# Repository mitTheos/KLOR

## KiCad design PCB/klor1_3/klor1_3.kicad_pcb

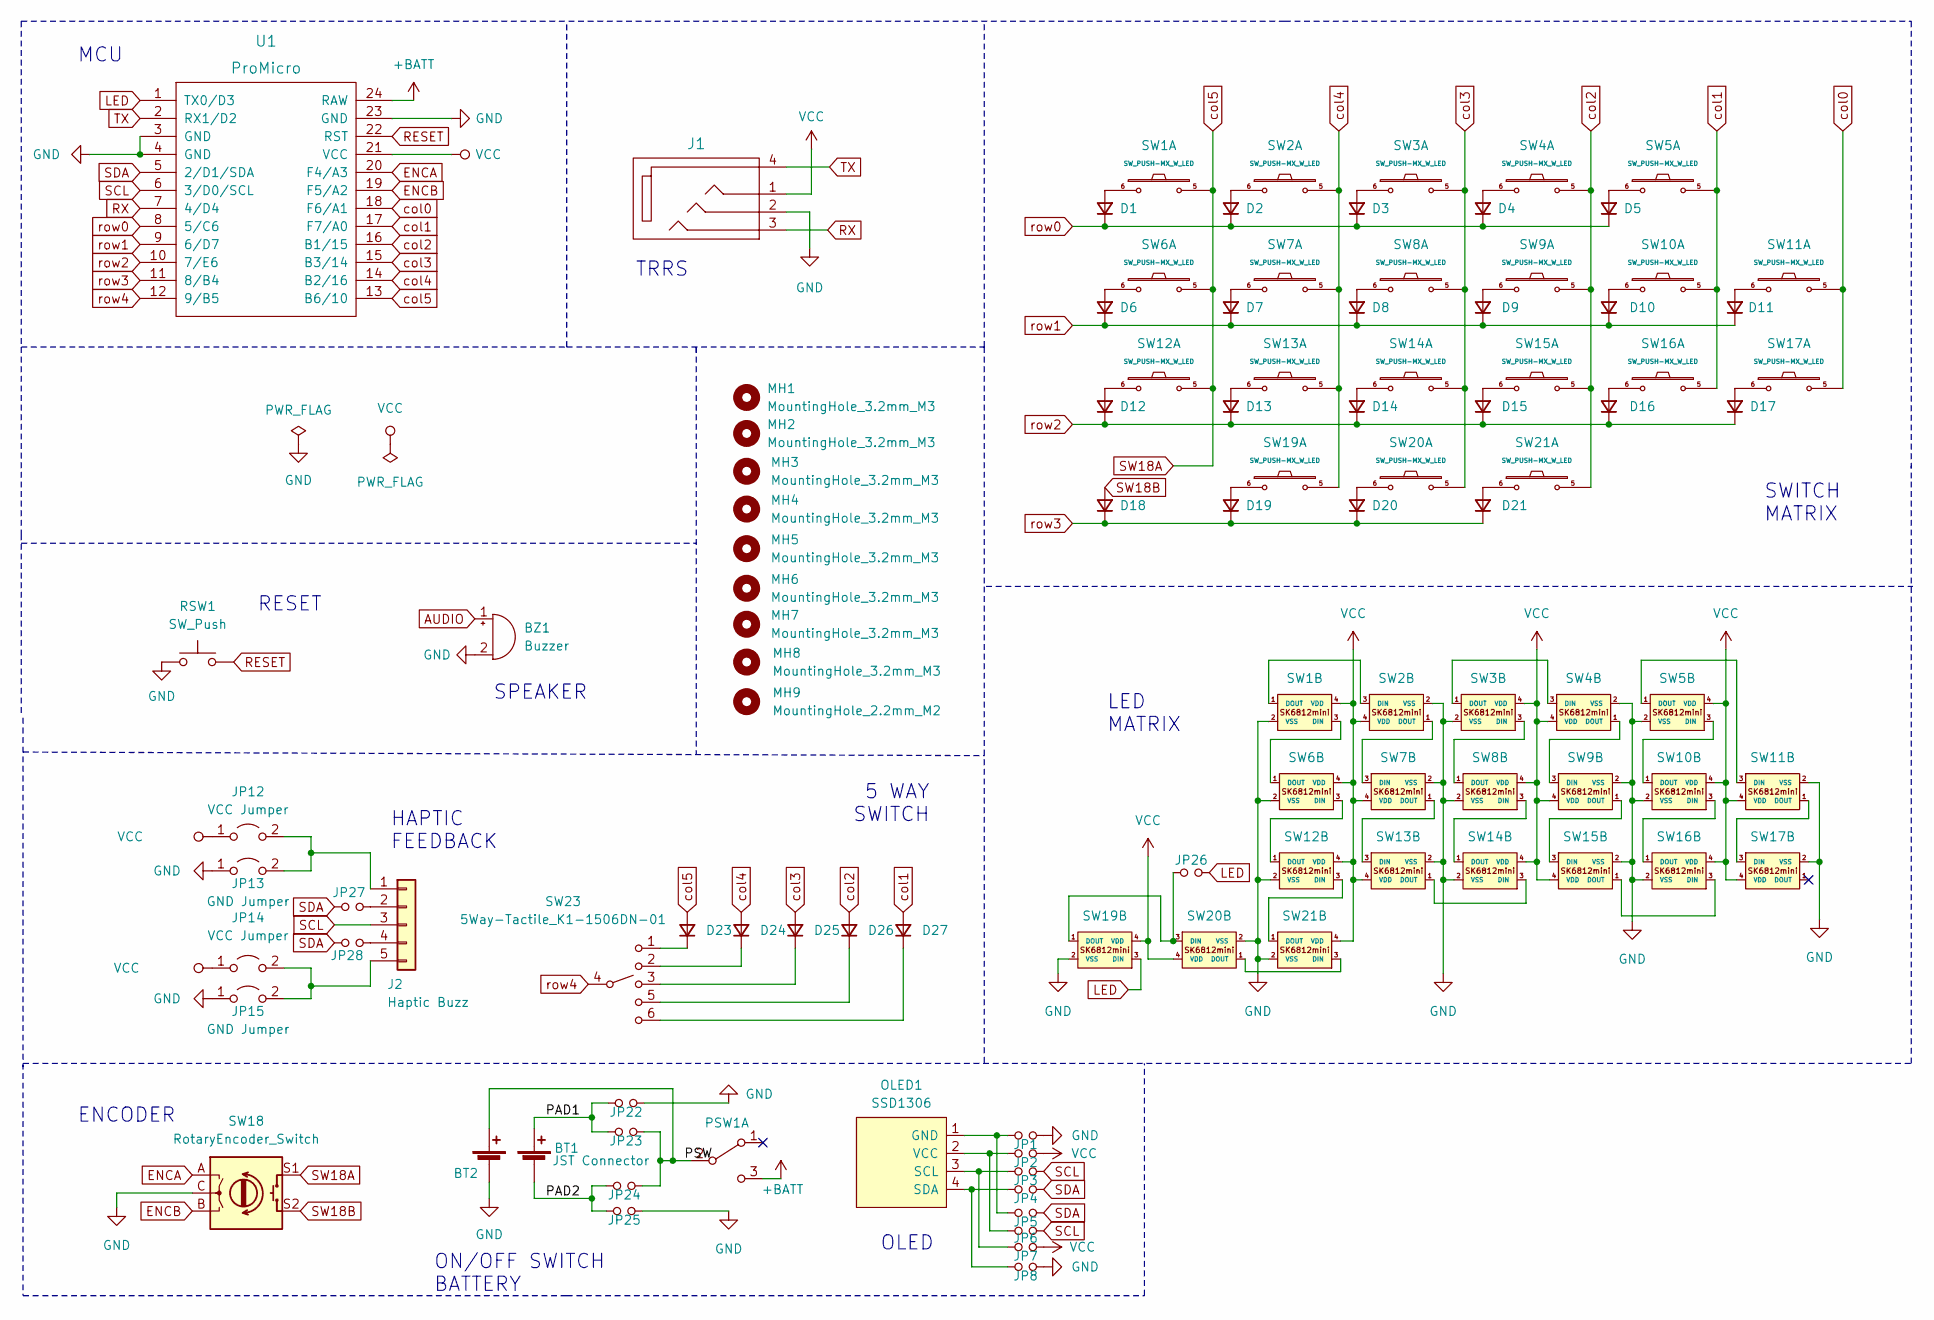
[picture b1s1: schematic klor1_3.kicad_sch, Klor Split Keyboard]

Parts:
BT1: JST Connector; JST_PH_reversible
BT2: Battery_Cell; custombatteryconnector_small
BZ1: Buzzer; Buzzer_Mallory_AST1109MLTRQ_reversible
D1, D2, D3, D4, D5, D6, D7, D8, D9, D10, D11, D12, D13, D14, D15, D16, D17, D18, D19, D20, D21, D23, D24, D25, D26, D27: D_Small; Diode_SOD123
J1: MJ-4PP-9
J2: Haptic Buzz; Pimoroni Haptic Buzz DRV2605L Driver
JP1, JP2, JP3, JP4, JP5, JP6, JP7, JP8, JP22, JP23, JP24, JP25, JP26, JP27, JP28: Device_Jumper_NO_Small; Jumper
JP12, JP14: VCC Jumper; Jumper
JP13, JP15: GND Jumper; Jumper
MH1, MH2, MH3, MH4, MH5, MH6, MH7, MH8: MountingHole_3.2mm_M3
MH9: MountingHole_2.2mm_M2
OLED1: SSD1306; SSD1306_128x64OLED
PSW1: SW_DPDT_x2; MSK12C02_reversible
RSW1: SW_Push; SW_Push_1P1T-MP_NO_Horizontal_Alps_SKRTLAE010_both_sides
SW1, SW2, SW3, SW4, SW5, SW6, SW7, SW8, SW9, SW10, SW11, SW12, SW13, SW14, SW15, SW16, SW17, SW19, SW20, SW21: SW_PUSH-MX_W_LED; SK6812MINI_and_cherry
SW18: RotaryEncoder_Switch; RotaryEncoder_Alps_EC11E-Switch_Vertical_H20mm-keebio_modif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
SW23: 5Way-Tactile_K1-1506DN-01; 5Way-K1-1506DN-01
U1: ProMicro

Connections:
+BATT: PSW1.3 (C), U1.24 (RAW)
/PAD1: BT1.1 (+), JP22.1, JP23.1
/PAD2: BT1.2 (-), JP24.1, JP25.1
/PSW: BT2.1 (+), JP23.2, JP24.2, PSW1.2 (B)
ENCA: SW18.A, U1.20 (F4/A3)
ENCB: SW18.B, U1.19 (F5/A2)
GND: BT2.2 (-), BZ1.2 (+), J1.2, JP1.2, JP8.2, JP13.1 (A), JP15.1 (A), JP22.2, JP25.2, RSW1.1, SW1.2 (VSS), SW2.2 (VSS), SW3.2 (VSS), SW4.2 (VSS), SW5.2 (VSS), SW6.2 (VSS), SW7.2 (VSS), SW8.2 (VSS), SW9.2 (VSS), SW10.2 (VSS), SW11.2 (VSS), SW12.2 (VSS), SW13.2 (VSS), SW14.2 (VSS), SW15.2 (VSS), SW16.2 (VSS), SW17.2 (VSS), SW18.C, SW19.2 (VSS), SW20.2 (VSS), SW21.2 (VSS), U1.3 (GND), U1.4 (GND), U1.23 (GND)
LED: JP26.2, SW19.3 (DIN), U1.1 (TX0/D3)
unnamed: D1.2 (A), SW1.6
unnamed: D2.2 (A), SW2.6
unnamed: D3.2 (A), SW3.6
unnamed: D4.2 (A), SW4.6
unnamed: D5.2 (A), SW5.6
unnamed: D6.2 (A), SW6.6
unnamed: D7.2 (A), SW7.6
unnamed: D8.2 (A), SW8.6
unnamed: D9.2 (A), SW9.6
unnamed: D10.2 (A), SW10.6
unnamed: D11.2 (A), SW11.6
unnamed: D12.2 (A), SW12.6
unnamed: D13.2 (A), SW13.6
unnamed: D14.2 (A), SW14.6
unnamed: D15.2 (A), SW15.6
unnamed: D16.2 (A), SW16.6
unnamed: D17.2 (A), SW17.6
unnamed: D19.2 (A), SW19.6
unnamed: D20.2 (A), SW20.6
unnamed: D21.2 (A), SW21.6
unnamed: D23.1 (K), SW23.1
unnamed: D24.1 (K), SW23.2
unnamed: D25.1 (K), SW23.3
unnamed: D26.1 (K), SW23.5
unnamed: D27.1 (K), SW23.6
unnamed: J2.1, JP12.2 (B), JP13.2 (B)
unnamed: J2.2, JP27.2
unnamed: J2.4, JP28.2
unnamed: J2.5, JP14.2 (B), JP15.2 (B)
unnamed: JP1.1, JP5.1, OLED1.1 (GND)
unnamed: JP3.1, JP7.1, OLED1.3 (SCL)
unnamed: JP4.1, JP8.1, OLED1.4 (SDA)
unnamed: JP2.1, JP6.1, OLED1.2 (VCC)
unnamed: SW1.3 (DIN), SW6.1 (DOUT)
unnamed: SW1.1 (DOUT), SW2.3 (DIN)
unnamed: SW2.1 (DOUT), SW7.3 (DIN)
unnamed: SW3.3 (DIN), SW8.1 (DOUT)
unnamed: SW3.1 (DOUT), SW4.3 (DIN)
unnamed: SW4.1 (DOUT), SW9.3 (DIN)
unnamed: SW10.3 (DIN), SW16.1 (DOUT)
unnamed: SW5.3 (DIN), SW10.1 (DOUT)
unnamed: SW5.1 (DOUT), SW11.3 (DIN)
unnamed: SW11.1 (DOUT), SW17.3 (DIN)
unnamed: SW12.3 (DIN), SW21.1 (DOUT)
unnamed: SW6.3 (DIN), SW12.1 (DOUT)
unnamed: SW7.1 (DOUT), SW13.3 (DIN)
unnamed: SW13.1 (DOUT), SW14.3 (DIN)
unnamed: SW8.3 (DIN), SW14.1 (DOUT)
unnamed: SW9.1 (DOUT), SW15.3 (DIN)
unnamed: SW15.1 (DOUT), SW16.3 (DIN)
unnamed: JP26.1, SW19.1 (DOUT), SW20.3 (DIN)
unnamed: SW20.1 (DOUT), SW21.3 (DIN)
RESET: RSW1.2, U1.22 (RST)
RX: J1.3, U1.7 (4/D4)
SCL: J2.3, JP3.2, JP6.2, U1.6 (3/D0/SCL)
SDA: JP4.2, JP5.2, JP27.1, JP28.1, U1.5 (2/D1/SDA)
SW18B: D18.2 (A), SW18.S2
TX: J1.4, U1.2 (RX1/D2)
VCC: J1.1, JP2.2, JP7.2, JP12.1 (A), JP14.1 (A), SW1.4 (VDD), SW2.4 (VDD), SW3.4 (VDD), SW4.4 (VDD), SW5.4 (VDD), SW6.4 (VDD), SW7.4 (VDD), SW8.4 (VDD), SW9.4 (VDD), SW10.4 (VDD), SW11.4 (VDD), SW12.4 (VDD), SW13.4 (VDD), SW14.4 (VDD), SW15.4 (VDD), SW16.4 (VDD), SW17.4 (VDD), SW19.4 (VDD), SW20.4 (VDD), SW21.4 (VDD), U1.21 (VCC)
col0: SW11.5, SW17.5, U1.18 (F6/A1)
col1: D27.2 (A), SW5.5, SW10.5, SW16.5, U1.17 (F7/A0)
col2: D26.2 (A), SW4.5, SW9.5, SW15.5, SW21.5, U1.16 (B1/15)
col3: D25.2 (A), SW3.5, SW8.5, SW14.5, SW20.5, U1.15 (B3/14)
col4: D24.2 (A), SW2.5, SW7.5, SW13.5, SW19.5, U1.14 (B2/16)
col5: D23.2 (A), SW1.5, SW6.5, SW12.5, SW18.S1, U1.13 (B6/10)
row0: D1.1 (K), D2.1 (K), D3.1 (K), D4.1 (K), D5.1 (K), U1.8 (5/C6)
row1: D6.1 (K), D7.1 (K), D8.1 (K), D9.1 (K), D10.1 (K), D11.1 (K), U1.9 (6/D7)
row2: D12.1 (K), D13.1 (K), D14.1 (K), D15.1 (K), D16.1 (K), D17.1 (K), U1.10 (7/E6)
row3: D18.1 (K), D19.1 (K), D20.1 (K), D21.1 (K), U1.11 (8/B4)
row4: SW23.4, U1.12 (9/B5)

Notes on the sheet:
SWITCH MATRIX
MCU
ON/OFF SWITCH BATTERY
HAPTIC FEEDBACK
ENCODER
OLED
LED MATRIX
5 WAY SWITCH
TRRS
RESET
SPEAKER

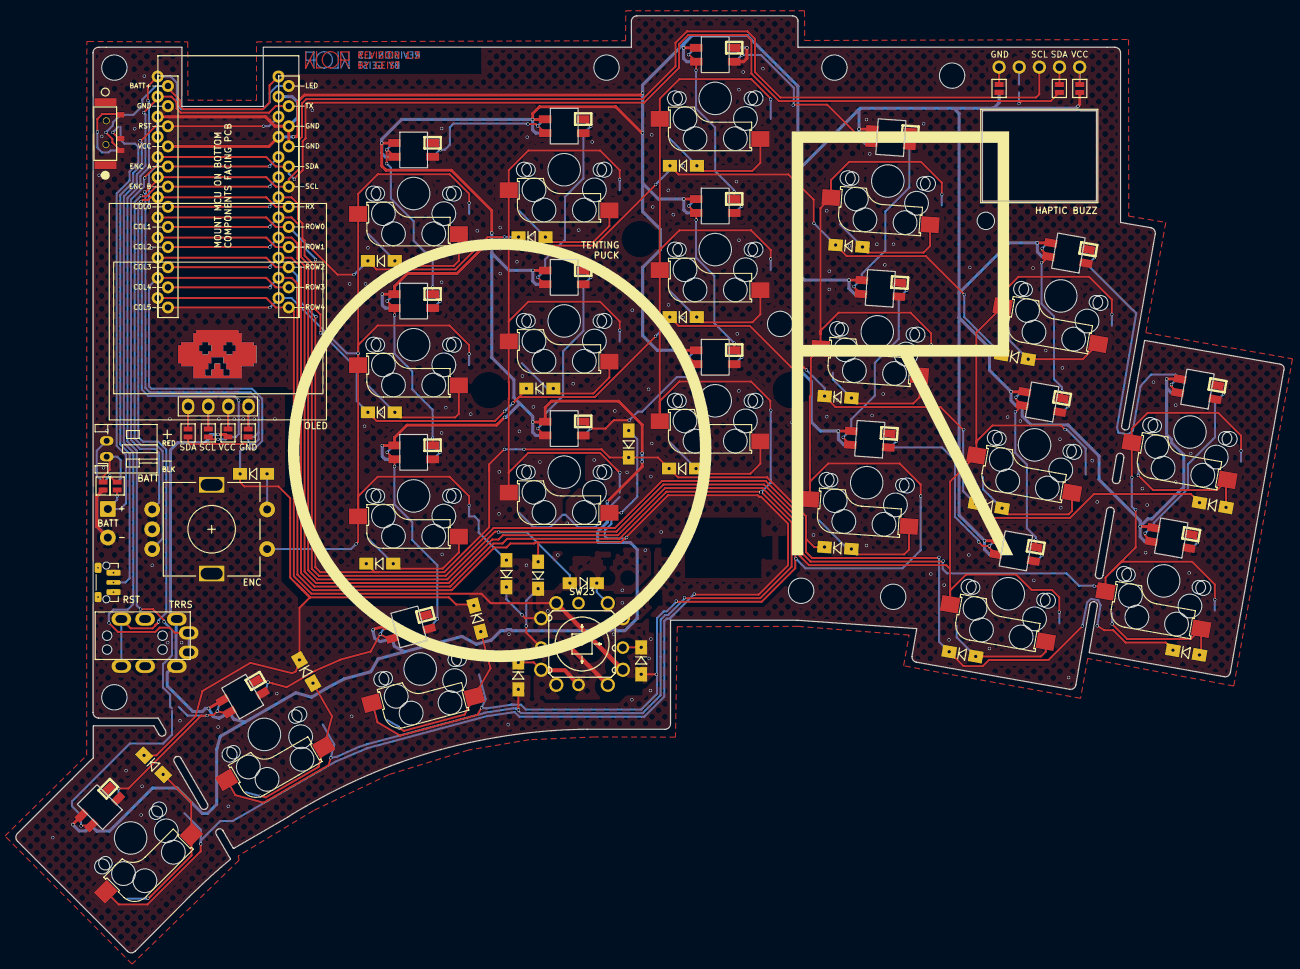
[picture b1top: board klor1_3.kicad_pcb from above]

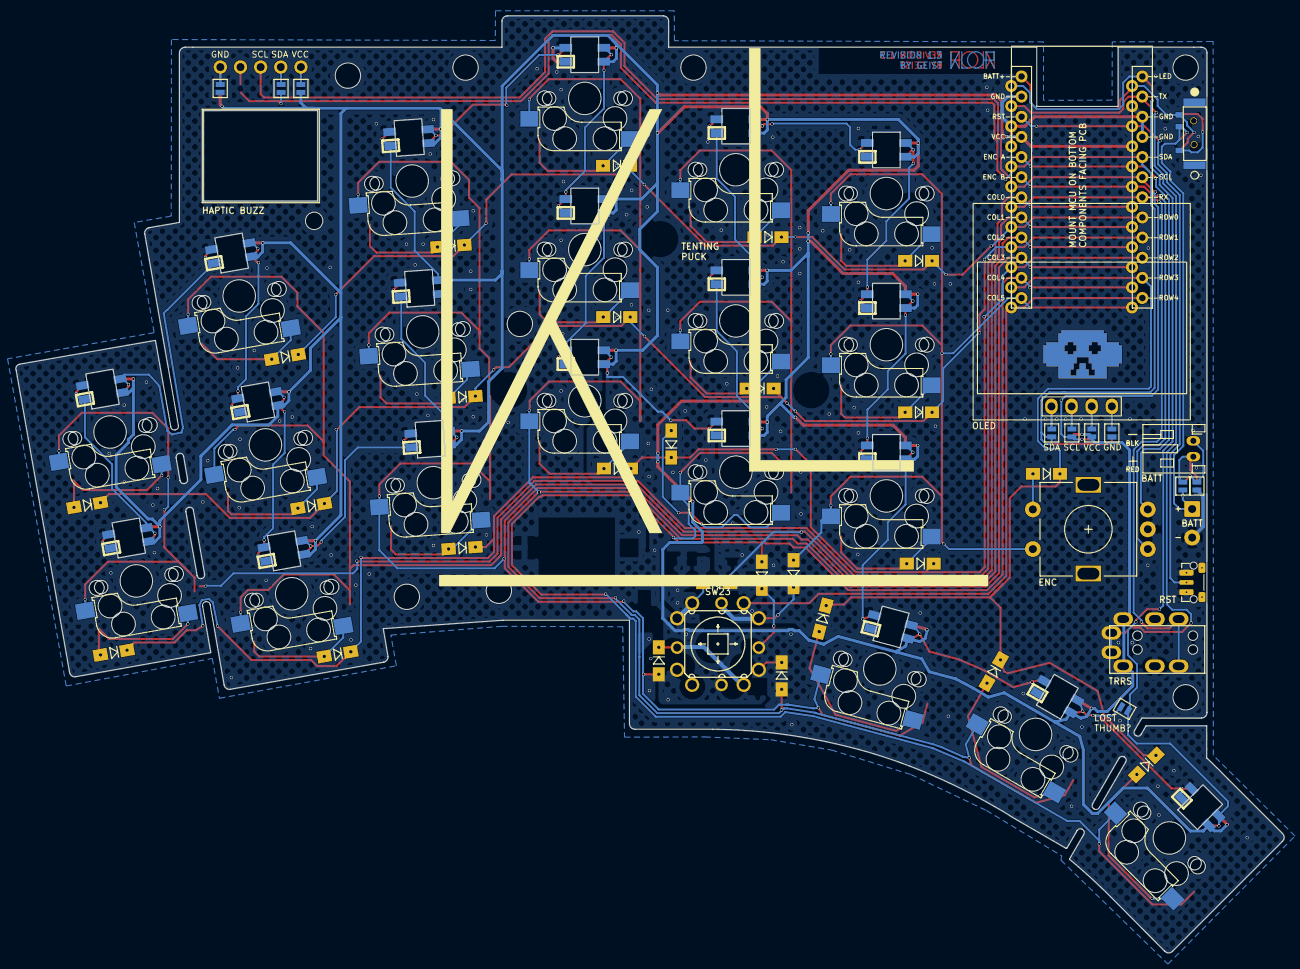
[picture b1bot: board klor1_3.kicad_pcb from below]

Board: 2 copper layers, 160.0 x 118.2 mm, 84 parts (11 on the bottom side), 78 nets.

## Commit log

2026-04-30 clean up PCB tracks
2026-04-30 update schematic with 5way switch
2026-04-30 add 5way switch to pcb TODO wires
2026-04-30 move and add label for 5way switch in schematic
2026-04-30 add routing of 5way switch to pcb
